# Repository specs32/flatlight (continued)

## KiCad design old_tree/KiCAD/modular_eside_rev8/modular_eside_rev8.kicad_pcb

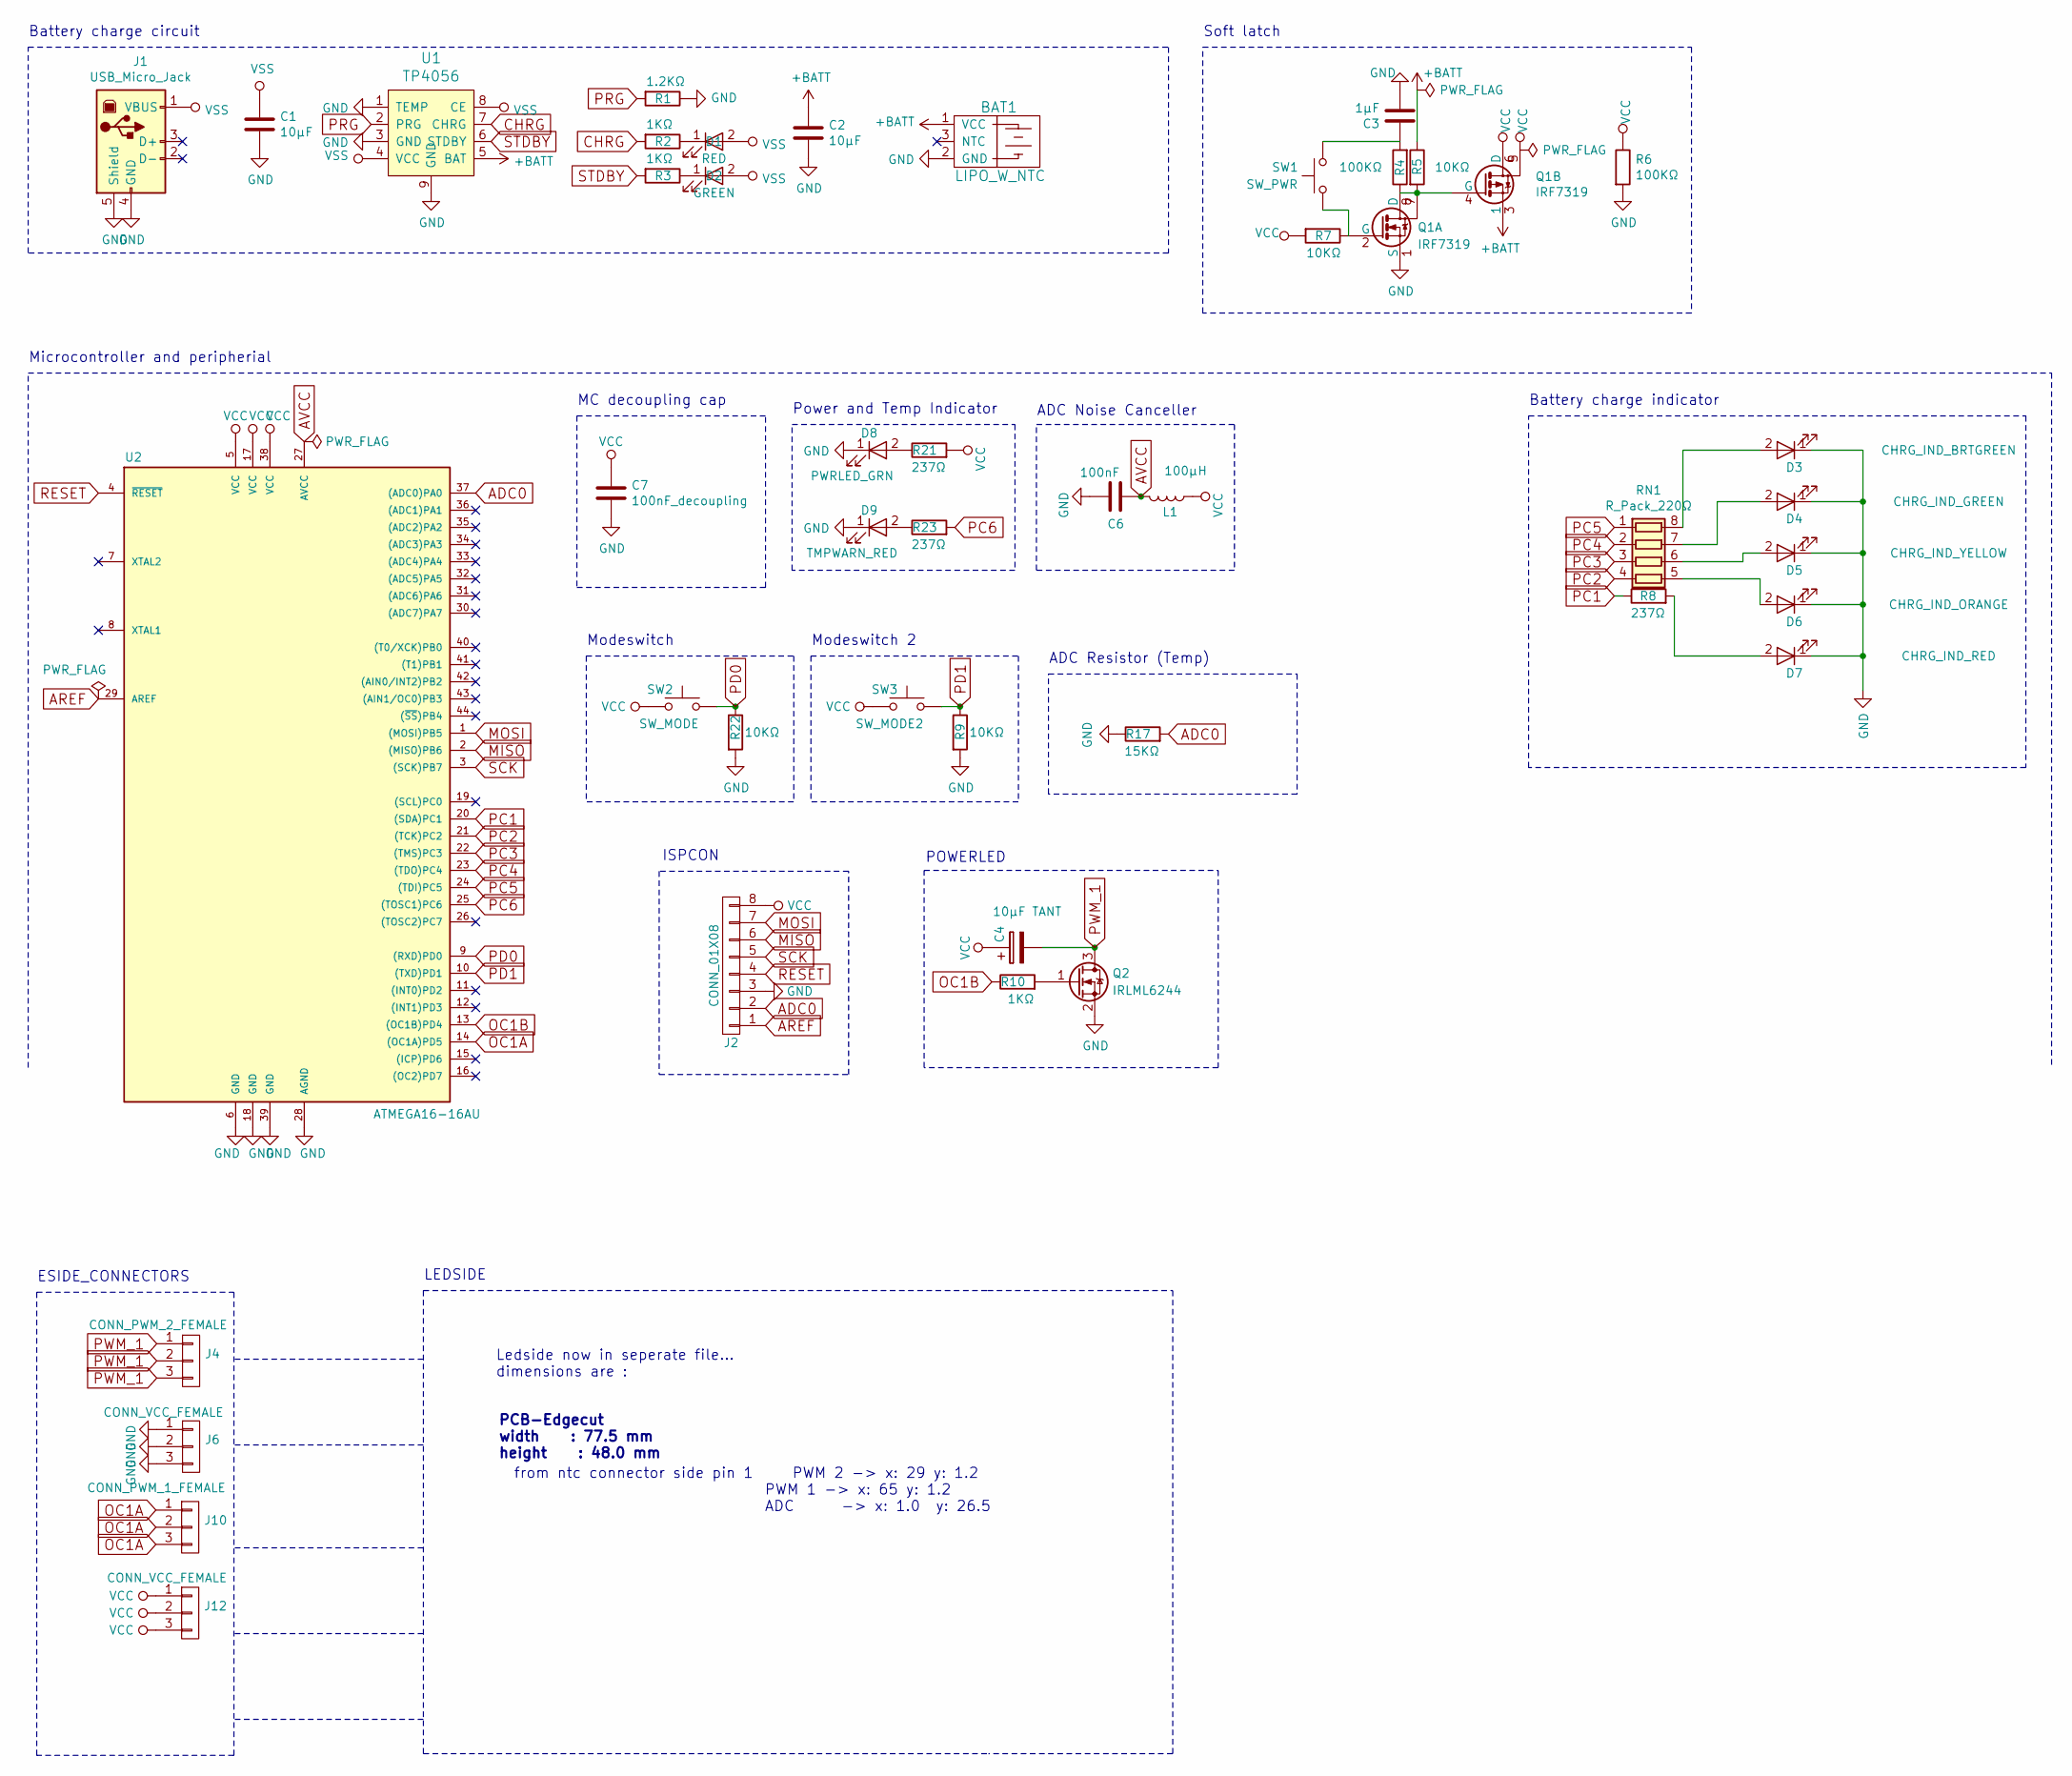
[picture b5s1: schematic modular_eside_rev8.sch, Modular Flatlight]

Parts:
BAT1: LIPO_W_NTC; conn_BST-41_spring_contact
C1, C2: 10µF; C_0805
C3: 1µF; C_0805
C4: 10µF TANT; C_1206
C6: 100nF; C_0805
C7: 100nF_decoupling; C_0805
D1: RED; LED_0603
D2: GREEN; LED_0603
D3: CHRG_IND_BRTGREEN; LED_0603
D4: CHRG_IND_GREEN; LED_0603
D5: CHRG_IND_YELLOW; LED_0603
D6: CHRG_IND_ORANGE; LED_0603
D7: CHRG_IND_RED; LED_0603
D8: PWRLED_GRN; LED_1206
D9: TMPWARN_RED; LED_0603
J1: USB_Micro_Jack; USB_Micro-B-CHINA
J2: CONN_01X08; 1x08_Pitch2.00mm_Bigpad
J4: CONN_PWM_2_FEMALE; 3pin_through_conn
J6, J12: CONN_VCC_FEMALE; 3pin_through_conn
J10: CONN_PWM_1_FEMALE; 3pin_through_conn
L1: 100µH; C_0805_HandSoldering
Q1: IRF7319; SOIC-8_3.9x4.9mm_Pitch1.27mm
Q2: IRLML6244; SOT-23
R1: 1.2KΩ; R_0805
R2, R3, R10: 1KΩ; R_0805
R4, R6: 100KΩ; R_0805
R5, R7, R9, R22: 10KΩ; R_0805
R8, R21, R23: 237Ω; R_0805
R17: 15KΩ; R_1210
RN1: R_Pack_220Ω; R_Array_Convex_4x0603
SW1: SW_PWR; red_button_mount_6.3mm
SW2: SW_MODE; red_button_mount_6.3mm
SW3: SW_MODE2; red_button_mount_6.3mm
U1: TP4056; SOIC-8-1EP_3.9x4.9mm_Pitch1.27mm
U2: ATMEGA16-16AU; TQFP-44_10x10mm_Pitch0.8mm_pad0.45

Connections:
+BATT: BAT1.1 (VCC), C2.1, Q1.3 (1), R5.1, U1.5 (BAT)
ADC0: J2.2, R17.2, U2.37 ((ADC0)PA0)
AREF: J2.1, U2.29 (AREF)
AVCC: C6.1, L1.2, U2.27 (AVCC)
CHRG: R2.2, U1.7 (CHRG)
GND: BAT1.2 (GND), C1.2, C2.2, C3.2, C6.2, C7.2, D3.1 (K), D4.1 (K), D5.1 (K), D6.1 (K), D7.1 (K), D8.1 (K), D9.1 (K), J1.4 (GND), J1.5 (Shield), J2.3, J6.1, J6.2, J6.3, Q1.1 (S), Q2.2 (S), R1.1, R6.2, R9.2, R17.1, R22.2, U1.1 (TEMP), U1.3 (GND), U1.9 (GND), U2.6 (GND), U2.18 (GND), U2.28 (AGND), U2.39 (GND)
MISO: J2.6, U2.2 ((MISO)PB6)
MOSI: J2.7, U2.1 ((MOSI)PB5)
unnamed: C3.1, R4.2, SW1.2
unnamed: D1.1 (K), R2.1
unnamed: D2.1 (K), R3.1
unnamed: D3.2 (A), RN1.8 (R1.2)
unnamed: D4.2 (A), RN1.7 (R2.2)
unnamed: D5.2 (A), RN1.6 (R3.2)
unnamed: D6.2 (A), RN1.5 (R4.2)
unnamed: D7.2 (A), R8.2
unnamed: D8.2 (A), R21.1
unnamed: D9.2 (A), R23.1
unnamed: Q1.2 (G), R7.1, SW1.1
unnamed: Q1.4 (G), Q1.7, Q1.8 (D), R4.1, R5.2
unnamed: Q2.1 (G), R10.2
OC1A: J10.1, J10.2, J10.3, U2.14 ((OC1A)PD5)
OC1B: R10.1, U2.13 ((OC1B)PD4)
PC1: R8.1, U2.20 ((SDA)PC1)
PC2: RN1.4 (R4.1), U2.21 ((TCK)PC2)
PC3: RN1.3 (R3.1), U2.22 ((TMS)PC3)
PC4: RN1.2 (R2.1), U2.23 ((TDO)PC4)
PC5: RN1.1 (R1.1), U2.24 ((TDI)PC5)
PC6: R23.2, U2.25 ((TOSC1)PC6)
PD0: R22.1, SW2.2, U2.9 ((RXD)PD0)
PD1: R9.1, SW3.2, U2.10 ((TXD)PD1)
PRG: R1.2, U1.2 (PRG)
PWM_1: C4.2, J4.1, J4.2, J4.3, Q2.3 (D)
RESET: J2.4, U2.4 (~RESET)
SCK: J2.5, U2.3 ((SCK)PB7)
STDBY: R3.2, U1.6 (STDBY)
VCC: C4.1, C7.1, J2.8, J12.1, J12.2, J12.3, L1.1, Q1.5, Q1.6 (D), R6.1, R7.2, R21.2, SW2.1, SW3.1, U2.5 (VCC), U2.17 (VCC), U2.38 (VCC)
VSS: C1.1, D1.2 (A), D2.2 (A), J1.1 (VBUS), U1.4 (VCC), U1.8 (CE)

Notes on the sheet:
Battery charge circuit
Soft latch
Microcontroller and peripherial
Power and Temp Indicator
Modeswitch
ADC Resistor (Temp)
MC decoupling cap
Battery charge indicator
ESIDE_CONNECTORS
LEDSIDE
Ledside now in seperate file... dimensions are :
PCB-Edgecut width : 77.5 mm height : 48.0 mm
from ntc connector side pin 1 PWM 2 -> x: 29 y: 1.2 PWM 1 -> x: 65 y: 1.2 ADC -> x: 1.0 y: 26.5
Modeswitch 2
ADC Noise Canceller
ISPCON
POWERLED

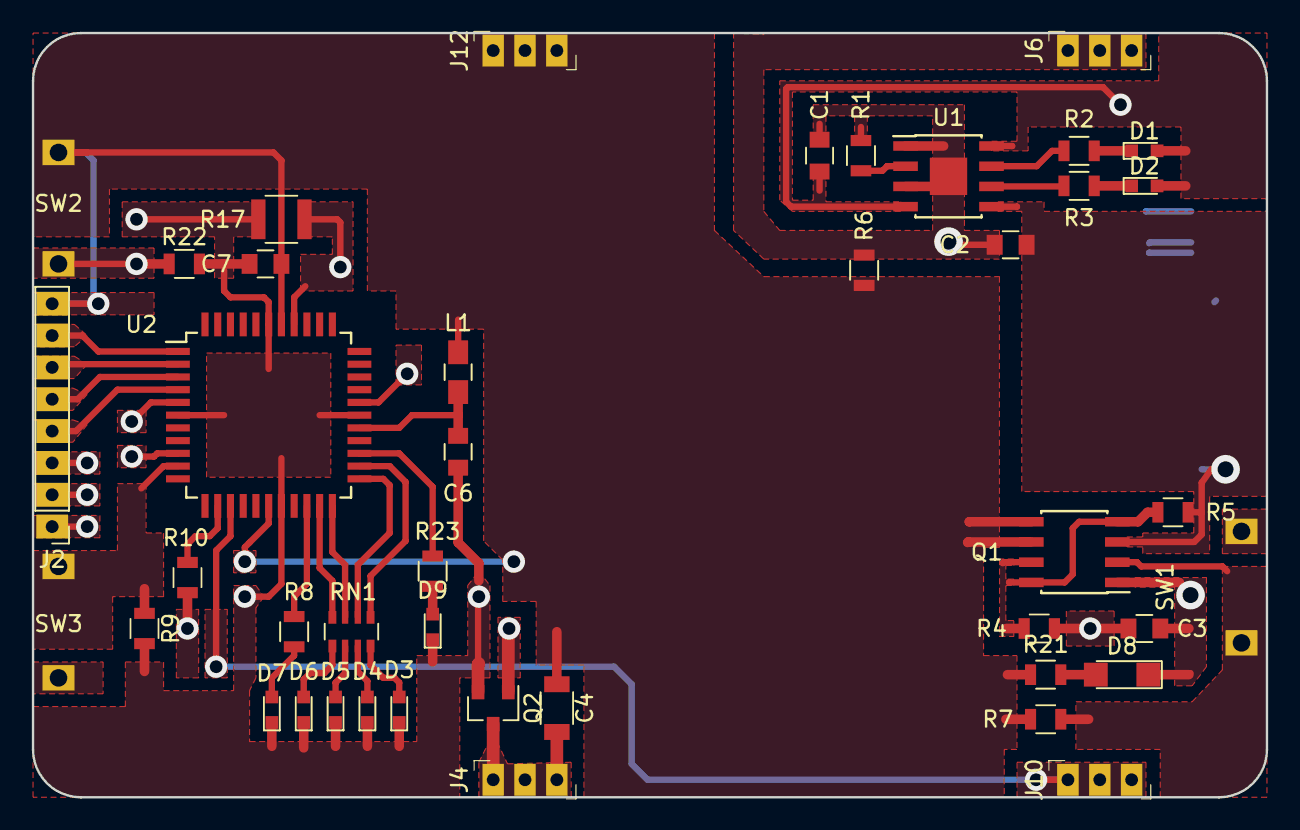
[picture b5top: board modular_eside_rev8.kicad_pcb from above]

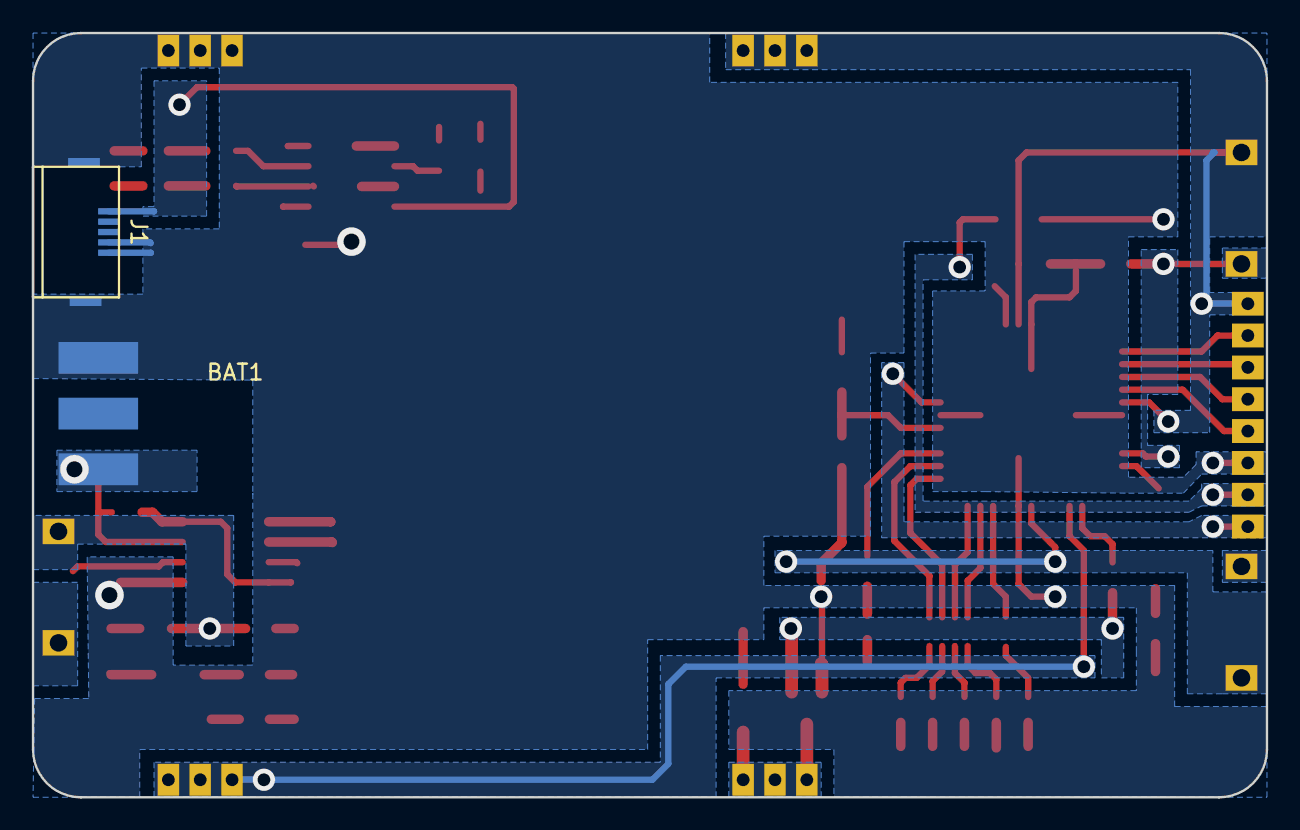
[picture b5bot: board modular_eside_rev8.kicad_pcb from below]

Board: 2 copper layers, 77.5 x 48.0 mm, 45 parts (2 on the bottom side), 38 nets.

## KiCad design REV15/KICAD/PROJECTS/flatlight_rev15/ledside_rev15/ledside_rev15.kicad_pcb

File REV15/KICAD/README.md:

/*

Flatlight Rev 15

    --- KiCad Files

*/

NOTE :

KiCAD is updated to Version 5.x

It should be possible to open the pcbnew files with a fresh KiCad install, 
just add the libs and footprints in the KiCad settings and youre good to go !

The Project Files are in the PROJECT folder ;)

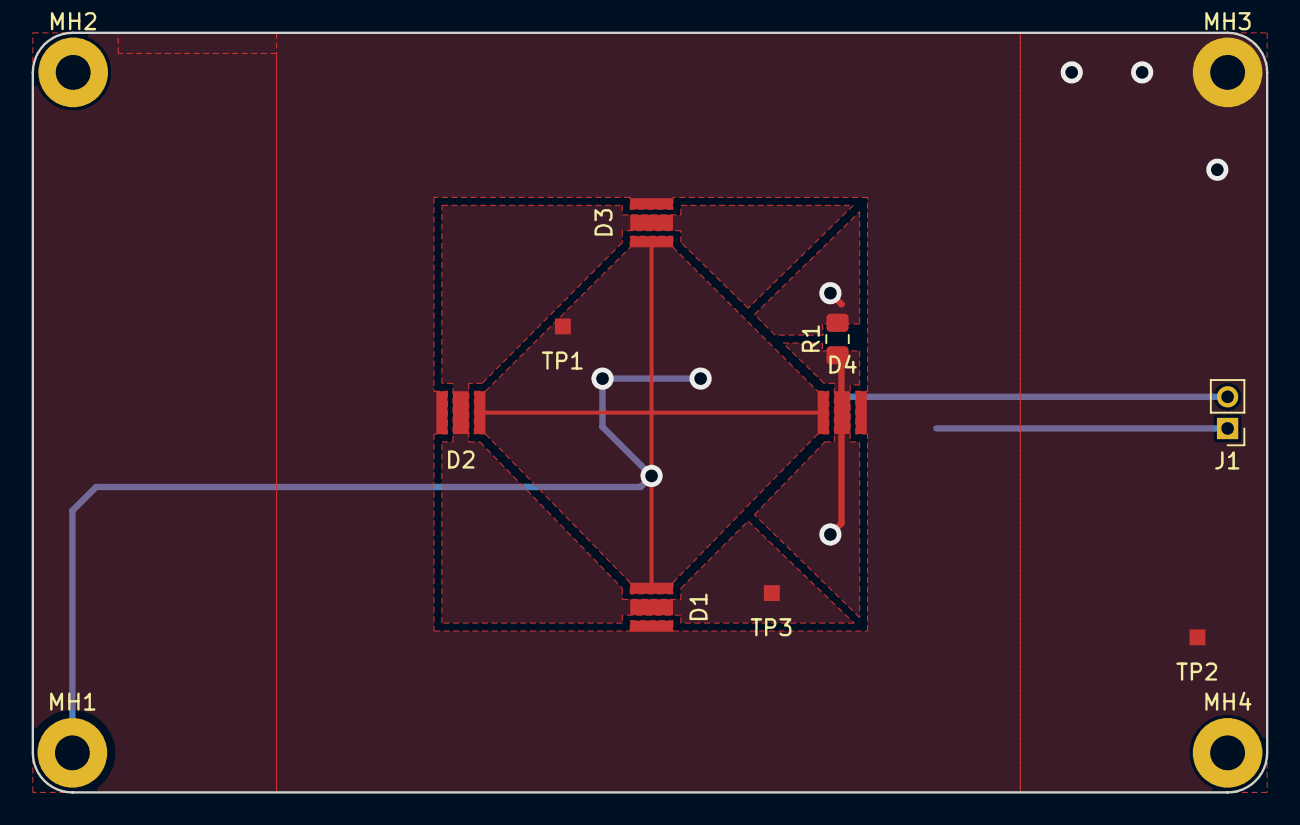
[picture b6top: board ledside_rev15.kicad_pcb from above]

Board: 2 copper layers, 78.0 x 48.0 mm, 13 parts (0 on the bottom side), 5 nets.

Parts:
D1, D2, D3, D4: LED; LED_osram_oslon_ssl_powerled
J1: Conn_01x02_Male; PinHeader_1x02_P2.00mm_Vertical
MH1: VCC; MountingHole_2.2mm_M2_Pad
MH2, MH4: GND; MountingHole_2.2mm_M2_Pad
MH3: SOURCE; MountingHole_2.2mm_M2_Pad
R1: R; R_0805_2012Metric_Pad1.15x1.40mm_HandSolder
TP1: VCC; 1_pad_smd
TP2: SOURCE; 1_pad_smd
TP3: THERM; 1_pad_smd

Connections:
GND: D1.1, D2.1, D3.1, D4.1, MH3.1, TP2.1
unnamed: D4.3, J1.1, R1.1
unnamed: J1.2, R1.2
VCC: D1.2, D2.2, D3.2, D4.2, MH1.1, TP1.1
therm: D1.3, D2.3, D3.3, TP3.1

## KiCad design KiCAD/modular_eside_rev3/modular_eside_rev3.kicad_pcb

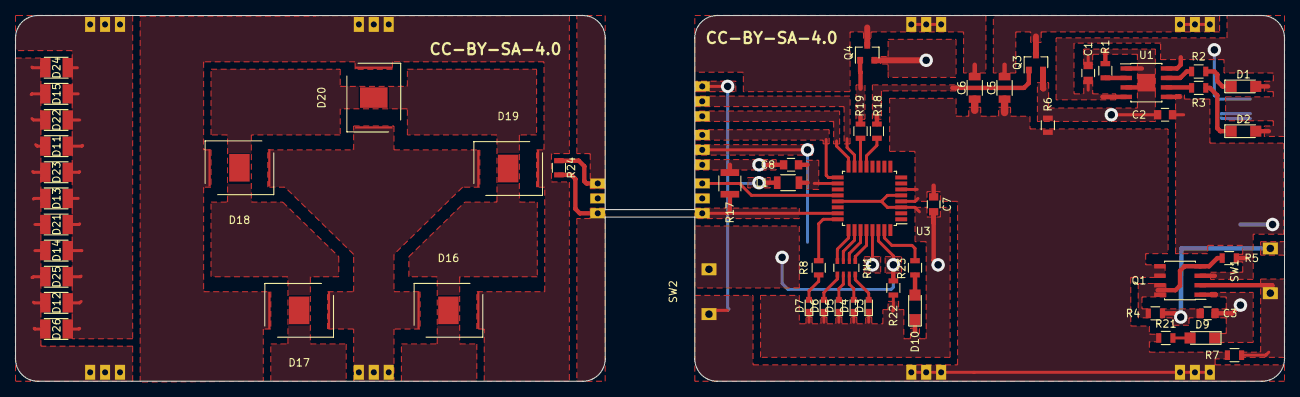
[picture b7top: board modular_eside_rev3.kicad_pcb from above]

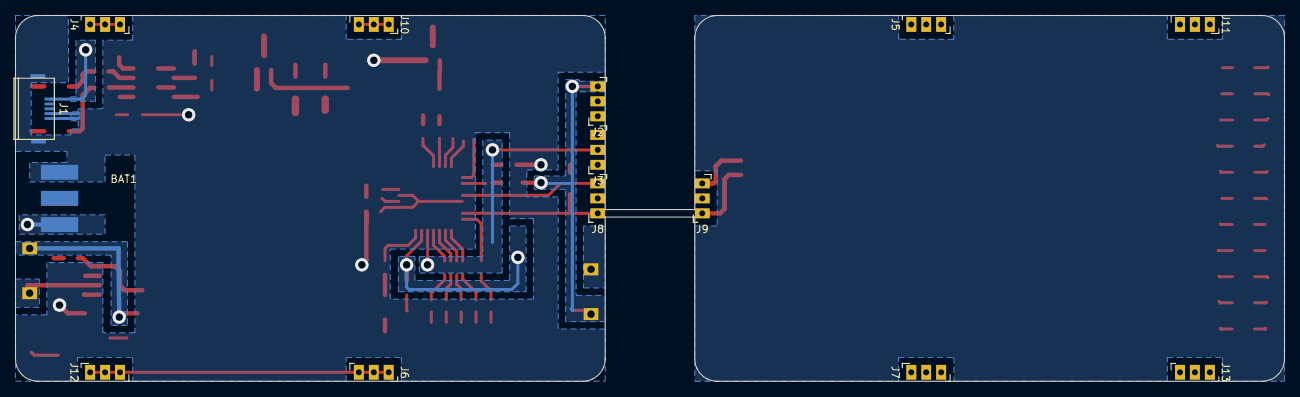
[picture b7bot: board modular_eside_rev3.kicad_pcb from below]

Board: 2 copper layers, 170.0 x 49.0 mm, 70 parts (14 on the bottom side), 45 nets.

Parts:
BAT1: LIPO_W_NTC; conn_BST-41_spring_contact
C1, C2: 10µF; C_0805
C3: 1µF; C_0805
C5, C6: 10µF; C_1206
C7: 100nF_decoupling; C_0805
C8: 100nF; C_0805
D1: RED; LED_1206
D2: GREEN; LED_1206
D3: CHRG_IND_BRTGREEN; LED_0603
D4: CHRG_IND_GREEN; LED_0603
D5: CHRG_IND_YELLOW; LED_0603
D6: CHRG_IND_ORANGE; LED_0603
D7: CHRG_IND_RED; LED_0603
D9: TOPLED_GRN; LED_1206
D10: RED_TMPWRN; LED_1206
D11, D12, D13, D14, D15, D21, D22, D23, D24, D25, D26: LED; LED_3528_new
D16, D17, D18, D19, D20: LED; LED_XR-C_CREE_9x7
J1: USB_Micro_Jack; USB_Micro-B-CHINA
J2: CONN_ES_ISP1; 3pin_through_conn
J3: CONN_ES_ISP2; 3pin_through_conn
J4: CONN_ES_LSGND; 3pin_through_conn
J5: CONN_LS_LSGND; 3pin_through_conn
J6: CONN_ES_VCC; 3pin_through_conn
J7: CONN_LS_VCC; 3pin_through_conn
J8: CONN_ES_NTC; 3pin_through_conn
J9: CONN_LS_NTC; 3pin_through_conn
J10, J11, J12, J13: CONN_BOARDCONN; 3pin_through_conn
L1: 10µH; L_1206
Q1: IRF7319; SOIC-8_3.9x4.9mm_Pitch1.27mm
Q3, Q4: IRLML6244; SOT-23
R1: 1.2KΩ; R_0805
R2, R3, R18, R19: 1KΩ; R_0805
R4, R6, R22: 100KΩ; R_0805
R5, R7: 10KΩ; R_0805
R8, R21, R23: 237Ω; R_0805
R17: 15KΩ; R_1210
R24: 15K NTC; R_0805
RN1: R_Pack_220Ω; R_Array_Convex_4x0603
SW1: SW_PWR; square_red_button_mount_6.3mm
SW2: SW_MODE; square_red_button_mount_6.3mm
U1: TP4056; SOIC-8-1EP_3.9x4.9mm_Pitch1.27mm
U3: ATMEGA8A-AU; TQFP-32_7x7mm_Pitch0.8mm

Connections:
+BATT: BAT1.1, C2.1, Q1.3, R5.1, U1.5
ADC0: J8.1, R17.2, U3.23
AREF: J8.3, U3.20
AVCC: C8.2, L1.2, U3.18
CHRG: R2.2, U1.7
GND: BAT1.2, C1.2, C2.2, C3.2, C7.2, C8.1, D3.1, D4.1, D5.1, D6.1, D7.1, D9.1, D10.1, J1.4, J1.5, J3.1, Q1.1, Q3.2, Q4.2, R1.1, R6.2, R17.1, R22.2, U1.1, U1.3, U1.9, U3.3, U3.5, U3.21
LED_ES_GND: C6.2, J10.1, J10.2, J10.3, Q4.3
LED_LS_GND: C5.2, J4.1, J4.2, J4.3, Q3.3
MISO: J2.1, U3.16
MOSI: J2.2, U3.15
unnamed: C3.1, R4.2, SW1.2
unnamed: D1.1, R2.1
unnamed: D2.1, R3.1
unnamed: D3.2, RN1.8
unnamed: D4.2, RN1.7
unnamed: D5.2, RN1.6
unnamed: D6.2, RN1.5
unnamed: D7.2, R8.2
unnamed: D9.2, R21.1
unnamed: D10.2, R23.1
unnamed: D11.1, D12.1, D13.1, D14.1, D15.1, D21.1, D22.1, D23.1, D24.1, D25.1, D26.1, J11.1, J11.2, J11.3
unnamed: D11.2, D12.2, D13.2, D14.2, D15.2, D21.2, D22.2, D23.2, D24.2, D25.2, D26.2, J13.1, J13.2, J13.3
unnamed: D16.1, D17.1, D18.1, D19.1, D20.1, J5.1, J5.2, J5.3
unnamed: D16.2, D17.2, D18.2, D19.2, D20.2, J7.1, J7.2, J7.3
unnamed: J9.1, R24.2
unnamed: J9.3, R24.1
unnamed: Q1.2, R7.1, SW1.1
unnamed: Q1.4, Q1.7, Q1.8, R4.1, R5.2
unnamed: Q3.1, R18.1
unnamed: Q4.1, R19.1
OC1A: R18.2, U3.13
OC1B: R19.2, U3.14
PC1: R8.1, U3.24
PC2: RN1.4, U3.25
PC3: RN1.3, U3.26
PC4: RN1.2, U3.27
PC5: RN1.1, U3.28
PD0: R22.1, SW2.2, U3.30
PD1: R23.2, U3.31
PRG: R1.2, U1.2
RESET: J3.2, U3.29
SCK: J3.3, U3.17
STDBY: R3.2, U1.6
VCC: C5.1, C6.1, C7.1, J2.3, J6.1, J6.2, J6.3, J12.1, J12.2, J12.3, L1.1, Q1.5, Q1.6, R6.1, R7.2, R21.2, SW2.1, U3.4, U3.6
VSS: C1.1, D1.2, D2.2, J1.1, U1.4, U1.8

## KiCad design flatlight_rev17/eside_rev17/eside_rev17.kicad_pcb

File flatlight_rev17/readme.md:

___REV17 changes___

LEDSIDE
- added LED Driver dio5661
- removed temp ntc
- routed pwm through 2 pin header (standoffs and screws only carry VCC and GND now)

ESIDE
- removed NTC network
- added cap ref -> GND
- routed pwm though 2 pin header
- added OLED (0.91" 128x32 ssd1306)
- added IMU  (LSM6D3)
- changed pixels to apa102-2020 chips
- fliped position of pixels and switches
- changed softlatch mosfet to dmc1030ubqf-7 (some tweaking required here for sure)
- changed µC to atmega328-p with qfn-32 footprint
- changed lithium charge management to dio5158

TODO
- create frames and buttons in blender
- create BOM
- correct pin orientation for 2 pin header (pwm signal) on ledside !!!!

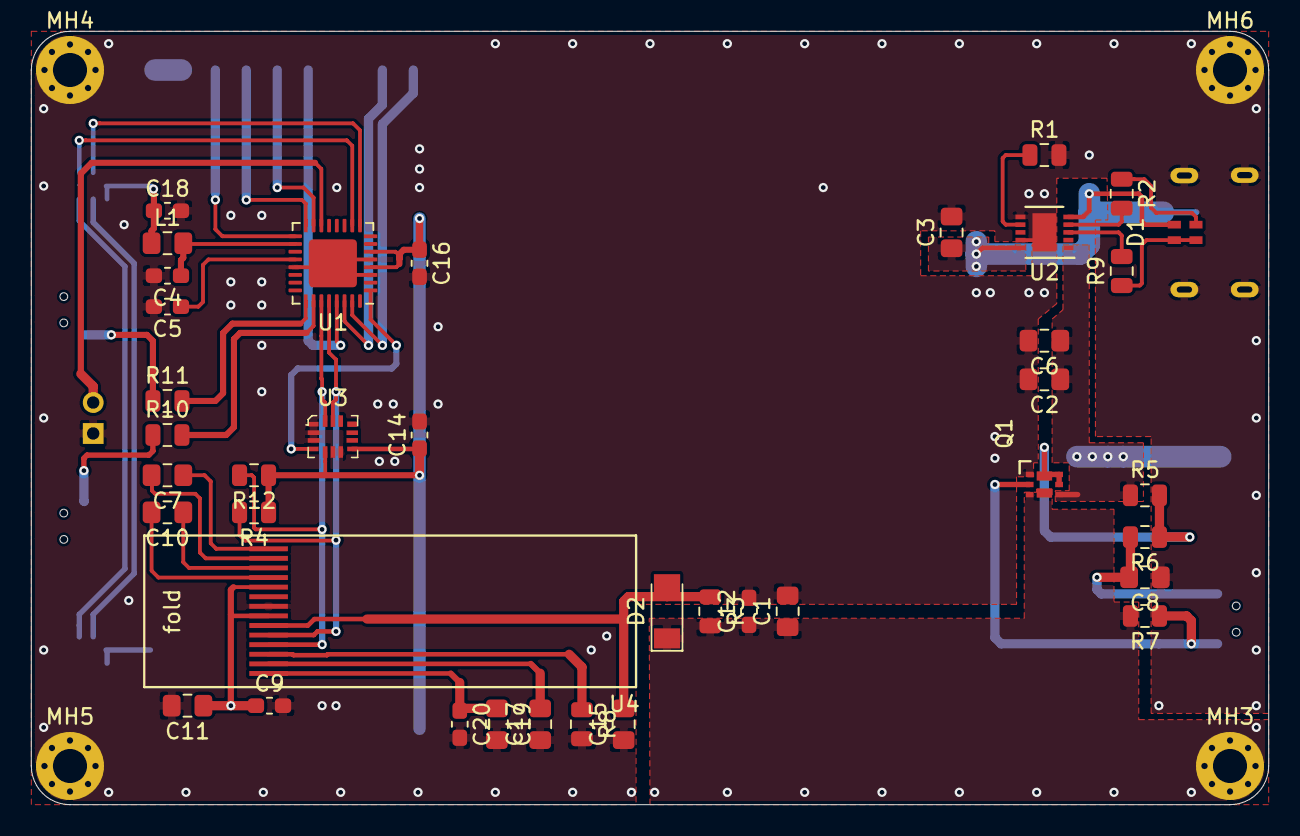
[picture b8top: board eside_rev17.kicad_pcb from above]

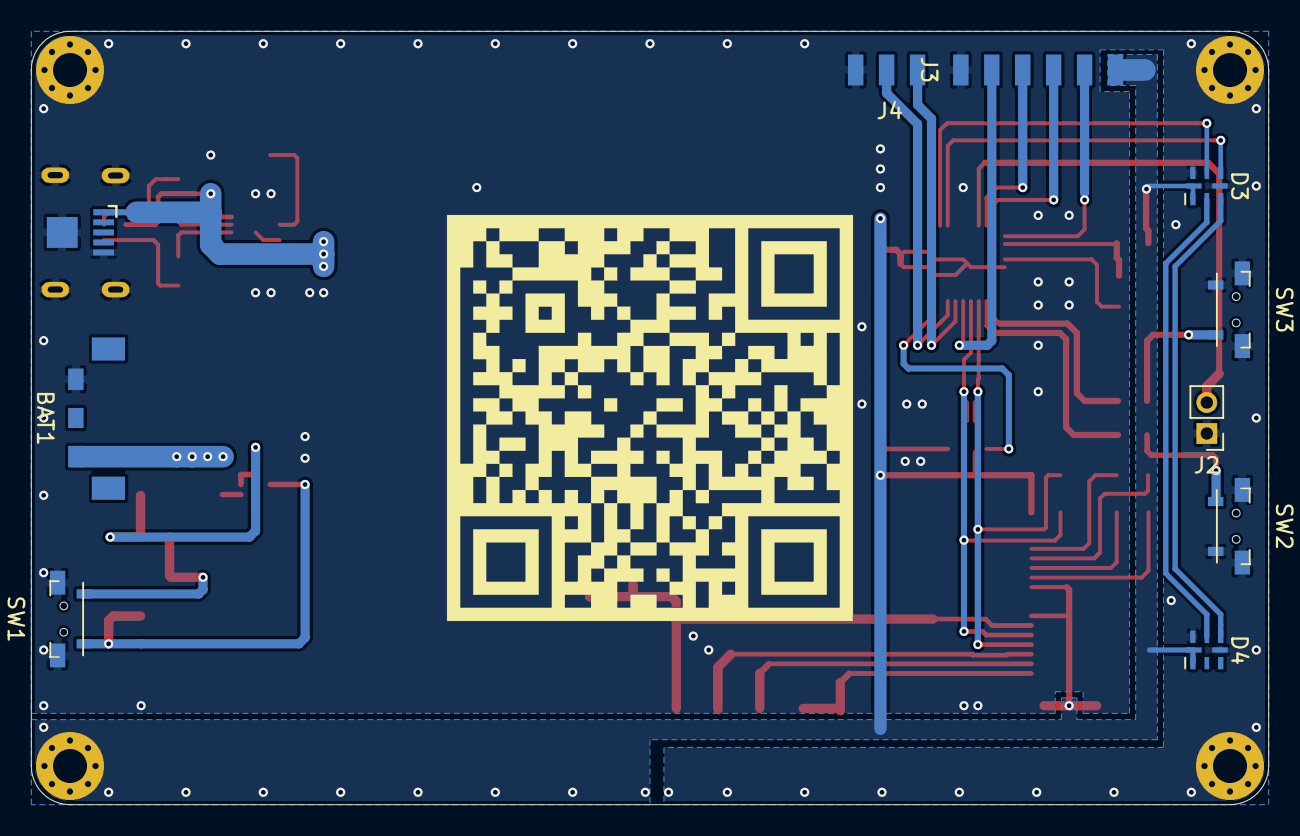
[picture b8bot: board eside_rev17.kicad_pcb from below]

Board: 2 copper layers, 80.0 x 50.0 mm, 57 parts (11 on the bottom side), 40 nets.

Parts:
BAT1: BST-41; CONN_AVX_RT_ANGLE_3pin_2.5mm_pitch
C1, C2, C3, C6, C11: 10µF; C_0805_2012Metric_Pad1.15x1.40mm_HandSolder
C4, C5, C9, C12, C14, C18, C20: 100nF; C_0603_1608Metric_Pad1.05x0.95mm_HandSolder
C7, C8, C10: 1µF; C_0805_2012Metric_Pad1.15x1.40mm_HandSolder
C15, C19: 4.7µF; C_0805_2012Metric_Pad1.15x1.40mm_HandSolder
C16: 100 nF; C_0603_1608Metric_Pad1.05x0.95mm_HandSolder
C17: 2.2µF; C_0805_2012Metric_Pad1.15x1.40mm_HandSolder
D1: LED_ARGB; LED_BARG_1.4x1.5mm
D2: LL4148; D_MiniMELF
D3, D4: APA102-2020; LED-APA102-2020
J1: USB_B_Micro; Conn_USBmicro-B_ebay-side_TH_GROUND
J2: Conn_OC1B-TEMP; PinHeader_1x02_P2.00mm_Vertical
J3: ISP_CONN; Conn_01x06_SMD_2mm
J4: Conn_SER; 01x03_smd_1mmx2mm_pad
L1: 10µH; L_0805_2012Metric_Pad1.15x1.40mm_HandSolder
MH3: VCC; MountingHole_2.2mm_M2_Pad_Via
MH4, MH5, MH6: GND; MountingHole_2.2mm_M2_Pad_Via
Q1: DMC1030UFDBQ; U-DFN2020-6 (Type B)
R1: 1.2kΩ; R_0805_2012Metric
R2, R9: 1kΩ; R_0805_2012Metric
R3: 4.7kΩ; R_0805_2012Metric
R4, R5, R7, R10, R11, R12: 10kΩ; R_0805_2012Metric
R6: 100kΩ; R_0805_2012Metric
R8: 380kΩ; R_0805_2012Metric
SW1, SW2, SW3: nano_switc_with_mnt_pads; white_nano_smd_switch
U1: ATmega328-MU; QFN-32-1EP_5x5mm_P0.5mm_EP3.1x3.1mm
U2: LIPOCHRG_Dio5158_DFN10; DFN-10-1EP_3x3mm_P0.5mm_EP1.55x2.48mm
U3: LSM6DS3TR; LGA-14L_2.5x3mm__LSM6DS3
U4: OLED_0.86_14PIN; OLED_0.86_14pin_i2c
dragon1: logo-dragon; logo_dragon_small
logo1: logo_contact; logo_QR-tag_rev16
logo2: logo_eside_rev17; logo_esiderev17
logo3: logo-cc-by-sa; cc-by-sa

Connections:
+BATT: BAT1.3, C2.1, C6.1, Q1.4, R5.1, U2.1
AVCC: C4.1, L1.2, U1.18
GND: BAT1.1, C1.2, C2.2, C3.2, C4.2, C5.2, C6.2, C8.1, C9.2, C11.2, C12.2, C14.2, C15.1, C16.2, C17.1, C18.2, C19.2, C20.2, D3.6, D4.6, J1.5, J1.6, J2.1, J3.1, J4.1, MH4.1, MH5.1, MH6.1, Q1.1, R1.2, R8.2, SW1.3, SW2.2, SW2.3, SW3.1, SW3.3, U1.3, U1.5, U1.21, U1.33, U2.6, U2.9, U2.11, U3.1, U3.2, U3.3, U3.6, U3.7, U4.7
MISO: J3.4, U1.16
MOSI: J3.3, U1.15
unnamed: C5.1, U1.20
unnamed: C7.1, U4.1
unnamed: C7.2, U4.2
unnamed: C8.2, R6.2, SW1.2
unnamed: C10.1, U4.3
unnamed: C10.2, U4.4
unnamed: C15.2, D2.2, R3.1, U4.9
unnamed: C17.2, U4.13
unnamed: C19.1, C20.1, U4.14
unnamed: D1.2, R2.1
unnamed: D1.3, D1.4, R9.1
unnamed: D3.2, D4.5
unnamed: D3.3, D4.4
unnamed: Q1.2, R7.1, SW1.1
unnamed: Q1.5, Q1.6, Q1.7, R5.2, R6.1
unnamed: R1.1, U2.7
unnamed: R2.2, U2.4
unnamed: R8.1, U4.12
unnamed: R9.2, U2.3
unnamed: R10.1, SW2.1
unnamed: R11.1, SW3.2
OC1B: J2.2, U1.14
PC2: R11.2, U1.25
PC3: R10.2, U1.26
PD3: U1.1, U3.4
PD5: D3.5, U1.9
PD6: D3.4, U1.10
RESET: J3.2, U1.29
RX: J4.3, U1.30
SCK: J3.5, U1.17
SCL: R4.2, U1.28, U3.13, U4.10
SDA: R12.2, U1.27, U3.14, U4.11
TX: J4.2, U1.31
VBUS: C3.1, D1.1, J1.1, U2.5, U2.10
VCC: C1.1, C9.1, C11.1, C12.1, C14.1, C16.1, C18.1, D2.1, D3.1, D4.1, J3.6, L1.1, MH3.1, Q1.3, Q1.8, R3.2, R4.1, R7.2, R12.1, U1.4, U1.6, U3.5, U3.8, U4.5, U4.8

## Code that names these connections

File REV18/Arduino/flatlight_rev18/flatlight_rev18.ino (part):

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const int BUTTON_DOWN = 16;                                  // define the down button pin

// LED PINS
const int LIGHT = 10;                                         // PowerLED PWM control. (OC1B // PB2 // PIN10)
const int BEAM = 9;                                           // PowerLED  PWM control. (OC1A // PB1 // PIN9)

// CONSTRAINS to the leds
uint8_t LIGHTPWMLIMIT = 150;                                  // PWMLIMIT FOR THE FULLY CHARGED LIPO !!!! 
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
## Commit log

2017-04-04 Add files via upload
    initial release
2017-04-04 the 1st commit
2017-04-04 committed
2017-09-15 eside revision 8 and neopixel matrix
    flatlight made for marvin with an atmega16a-au.
    layout for neopixel and cree xp something power led on ledside.
    dedicated battery check and temperature control.
2017-11-05 Added Test functionality for the ProLib (More in the Readme.txt)
2017-11-06 new file: KiCAD/FOOTPRINTS/ESP32-footprints-Lib.pretty/ESP32-WROOM.kicad_mod new file: KiCAD/FOOTPRINTS/ESP32-footprints-Lib.pretty/ESP32.kicad_mod new file: KiCAD/FOOTPRINTS/ESP32-footprints-Lib.pre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
2017-11-06 Last Commit
2017-11-12 Added LED Matrix controls
2017-11-13 comment
2018-09-01 Set theme jekyll-theme-cayman
2018-09-01 changed tree and added Rev15
2018-09-01 Set theme jekyll-theme-minimal
2018-09-01 Some deletions
2019-07-13 Add files via upload
    rev17
2019-07-13 Create readme.md
    changes
2019-07-13 Add files via upload
    integrated IMU
2019-07-15 Added Blender history
2019-07-15 Updated Structure
2019-07-16 updated blender and arduino
2019-12-23 flatlight revision 18 A
2019-12-23 updated blender files
    added frame modifications for headband use in REV 17
2020-01-16 updated REV18
2020-01-16 updated kiCAD
